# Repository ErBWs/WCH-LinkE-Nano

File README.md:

# WCH-LinkE-Nano

 自制WCH-LinkE

## 使用教程

1. 准备好一个WCH-Link，可以考虑我之前制作的[这款](https://oshwhub.com/erbw_s/wch-link)。

   > 这个下载器需要另一个wch-link才可以自制，很麻烦所以我一开始没考虑，但是下载速度的确很快

2. 直接打开`3.Software`文件夹内的`WCH-LinkUtility.exe`

3. 载入`2.Firmware`内的`.bin`文件并烧录

4. 断电重新上电即可作为正常WCH-LinkE使用

5. 持续按住MODE键上电，等待一段时间后松开可在`Link-RV`和`DAP`模式中切换

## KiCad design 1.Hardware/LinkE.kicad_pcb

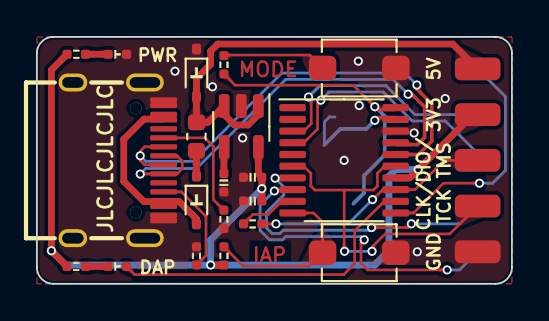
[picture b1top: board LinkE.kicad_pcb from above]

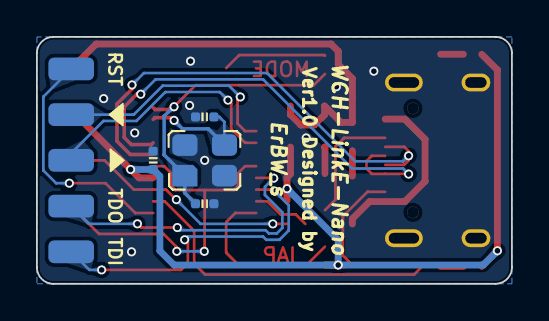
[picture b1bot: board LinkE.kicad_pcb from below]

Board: 2 copper layers, 26.4 x 13.7 mm, 25 parts (4 on the bottom side), 25 nets.

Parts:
C1, C8: 100nF; C_0402
C2: 10uF; C_0402
C3: 10nF; C_0402
C4, C5: 22pF; C_0402
D1: GREEN; LED_0402
D2: ESD; SOD-323
D3: 1N5819; SOD-323
D4: BLUE; LED_0402
F1: 500mA; Fuse_0603_1608Metric
J2: Conn_02x05_Odd_Even; Debug_Header_2x05
J?: USB-Type-C; USB-Type-C_SMD_16P
R1, R2: 4.7K; R_0402
R3, R4, R6: 10K; R_0402
R5: 1K; R_0402
R7: 0R; R_0402
SW1: ModeS; BUTTON_3x4
SW2: IAP; BUTTON_3x4
U1: RT9013-33GB; SOT-23-5
U2: CH32V305FBT6; TSSOP-20_4.4x6.5mm_P0.65mm
Y1: 12MHz; Crystal_SMD_3225_4P

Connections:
+3.3V: C1.1, C2.1, C8.1, J2.3, R3.1, R4.1, R6.1, U1.5 (VOUT), U2.14 (VDD33/VIO)
+5V: D3.2 (A), J?.A4 (VBUS), J?.A9 (VBUS), J?.B4 (VBUS), J?.B9 (VBUS)
+5VA: D2.2 (A2), F1.2, J2.1, U1.1 (VIN), U1.3 (EN)
/IAP: R6.2, SW2.1, U2.10 (PC7)
/LED_CON: D4.2 (A), U2.12 (PC9/PA8/UART1_RX)
/OSC_N: C4.1, R7.1, U2.20 (OSC_OUT/PD1), Y1.1
/OSC_P: C5.1, U2.19 (OSC_IN/PD0), Y1.3
/RST: J2.2, U2.11 (PC8)
/RX: J2.6, U2.4 (PB11/UART3_RX/I2C2_SDA)
/SWCLK: J2.7, U2.6 (PB13/SPI2_SCK/UART3_CTS/CAN2_TX), U2.15 (PA14/SWCLK)
/SWDIO: J2.5, R5.1, U2.13 (PA9/UART1_RTS/PA13/SWDIO)
/TDI: J2.10, U2.8 (PB15/SPI2_MOSI/UART1_TX)
/TDO: J2.8, U2.7 (PB14/SPI2_MISO/UART3_RTS)
/TX: J2.4, U2.3 (PB10/UART3_TX/I2C2_SCL)
/USB_N: J?.A7 (D-), J?.B7 (D-), U2.16 (PB6/USB2DM/UART1X_TX)
/USB_P: J?.A6 (D+), J?.B6 (D+), U2.17 (PB7/USB2DP/UART1X_RX)
GND: C1.2, C2.2, C3.2, C4.2, C5.2, C8.2, D1.2 (A), D2.1 (A1), J2.9, J?.A1 (GND), J?.A12 (GND), J?.B1 (GND), J?.B12 (GND), J?.S1 (SH), R1.2, R2.2, SW1.2, SW2.2, U1.2 (GND), U2.18 (VSS/GND), Y1.2, Y1.4
unnamed: D1.1 (K), R3.2
unnamed: D3.1 (K), F1.1
unnamed: D4.1 (K), R4.2
unnamed: J?.A5 (CC1), R1.1
unnamed: J?.B5 (CC2), R2.1
unnamed: R7.2, SW1.1
unnamed: C3.1, U1.4 (NC)
unnamed: R5.2, U2.9 (PC6)

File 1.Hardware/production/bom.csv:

Designator,Footprint,Quantity,Value,LCSC Part #
"C1, C8",C_0402,2,100nF,
C2,C_0402,1,10uF,
C3,C_0402,1,10nF,
"C4, C5",C_0402,2,22pF,
D1,LED_0402,1,GREEN,
D2,SOD-323,1,ESD,
D3,SOD-323,1,1N5819,
D4,LED_0402,1,BLUE,
F1,0603,1,500mA,
J1,USB-Type-C_SMD_16P,1,USB-Type-C,
J2,Debug_Header_2x05,1,Conn_02x05_Odd_Even,
"R1, R2",R_0402,2,4.7K,
"R3, R4, R6",R_0402,3,10K,
R5,R_0402,1,1K,
R7,R_0402,1,0R,
SW1,BUTTON_3x4,1,ModeS,
SW2,BUTTON_3x4,1,IAP,
U1,SOT-23-5,1,RT9013-33GB,
U2,TSSOP-20_4.4x6.5mm_P0.65mm,1,CH32V305FBT6,
Y1,Crystal_SMD_3225_4P,1,12MHz,

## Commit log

2023-04-21 Update files
2025-04-24 add docs
